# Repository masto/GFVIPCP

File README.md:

# Glowforge Pentagonal Hexecontahedron

These are the "source files" for the tile I made as part of
[this project](https://community.glowforge.com/t/pentagonal-hexecontahedron/58099).

Mine's the one with the USB port. It flashes some light patterns when you plug it in.

More in this video:

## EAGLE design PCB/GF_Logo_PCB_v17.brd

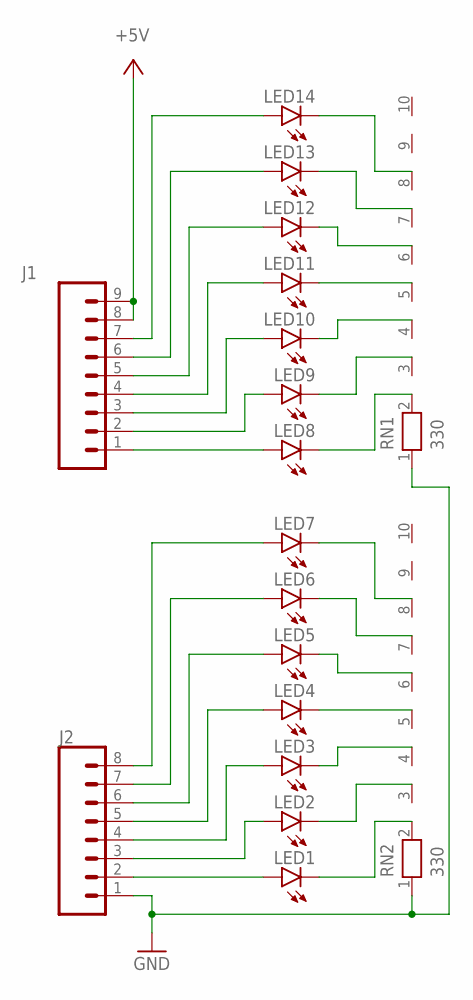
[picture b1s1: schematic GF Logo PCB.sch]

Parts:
J1: CONN_09; 1X09
J2: CONN_08"; 1X08
LED1, LED2, LED3, LED4, LED5, LED6, LED7, LED8, LED9, LED10, LED11, LED12, LED13, LED14: Grn; LED3MM
RN1, RN2: 330; RN-10

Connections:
+5V: J1.8, J1.9
GND: J2.1, RN1.1, RN2.1
unnamed: LED1.K (C), RN2.2
unnamed: LED2.K (C), RN2.3
unnamed: LED3.K (C), RN2.4
unnamed: LED4.K (C), RN2.5
unnamed: LED5.K (C), RN2.6
unnamed: LED6.K (C), RN2.7
unnamed: LED7.K (C), RN2.8
unnamed: J2.2, LED1.A
unnamed: J2.3, LED2.A
unnamed: LED8.K (C), RN1.2
unnamed: LED9.K (C), RN1.3
unnamed: LED10.K (C), RN1.4
unnamed: LED11.K (C), RN1.5
unnamed: LED12.K (C), RN1.6
unnamed: LED13.K (C), RN1.7
unnamed: J2.4, LED3.A
unnamed: J2.5, LED4.A
unnamed: J2.6, LED5.A
unnamed: J2.7, LED6.A
unnamed: J2.8, LED7.A
unnamed: LED14.K (C), RN1.8
unnamed: J1.1, LED8.A
unnamed: J1.2, LED9.A
unnamed: J1.3, LED10.A
unnamed: J1.4, LED11.A
unnamed: J1.5, LED12.A
unnamed: J1.6, LED13.A
unnamed: J1.7, LED14.A

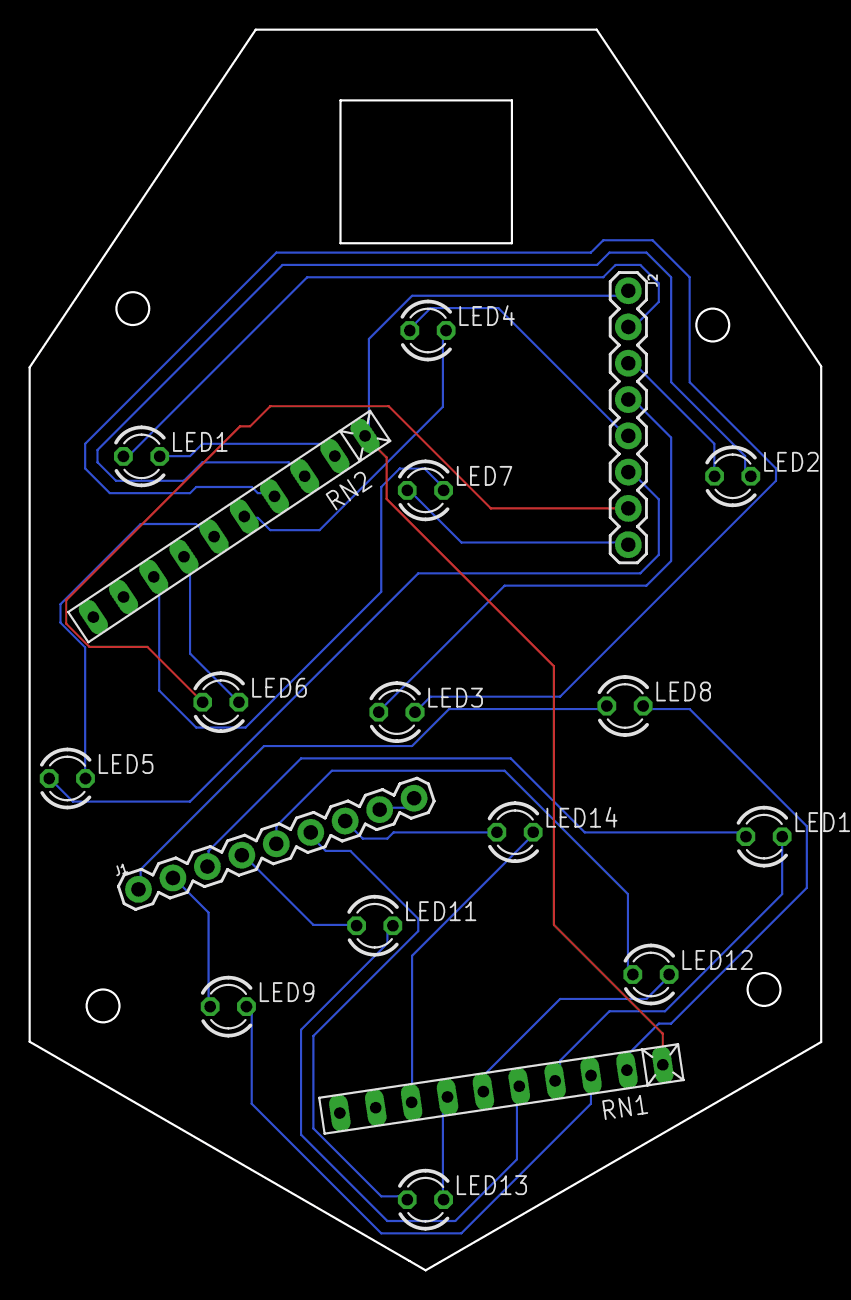
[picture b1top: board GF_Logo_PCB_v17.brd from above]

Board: 2 copper layers, 55.4 x 86.9 mm, 18 parts (0 on the bottom side), 30 nets.

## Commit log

2020-05-29 Export Fusion 360 files for safe keeping

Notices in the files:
parts and their libraries:
SparkFun-Connectors: Licensing: Creative Commons ShareAlike 4.0 International - https://creativecommons.org/licenses/by-sa/4.0
